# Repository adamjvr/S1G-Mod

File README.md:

# S1G-Mod
A Sub 1GHZ Wireless Module for various Sub 1GHZ projects and applications
Hardware Specs
- ADF7023 RF Transceiver
- 28 Mile line of site range
- Dedicated Antennas for RX and TX
- Open Source under CERN Open Hardware License v1.2 (Included)
- Circuitry shielded with outer shield.
- UM Coaxial Antenna connectors
- STM32L052C8T6 ARM Cortex M0+
- USB 2.0 connectivity
- USART connectivity
- SPI connectivity
- USB bus or battery powered
- Combined and Separate PA/LNA Match versions of 915MHZ and 433MHZ modules

Firmware and development at:
https://github.com/adamjvr/S1G-RF-firmwware

Combined RX/TX S1G-RF Module:

KiCAD 3D OpenGL

Separate RX/TX S1G-RF Module:

KiCAD 3D OpenGL

Adapters:

USART JST Adapter

SPI JST Adapter

Adapter Test Fit:

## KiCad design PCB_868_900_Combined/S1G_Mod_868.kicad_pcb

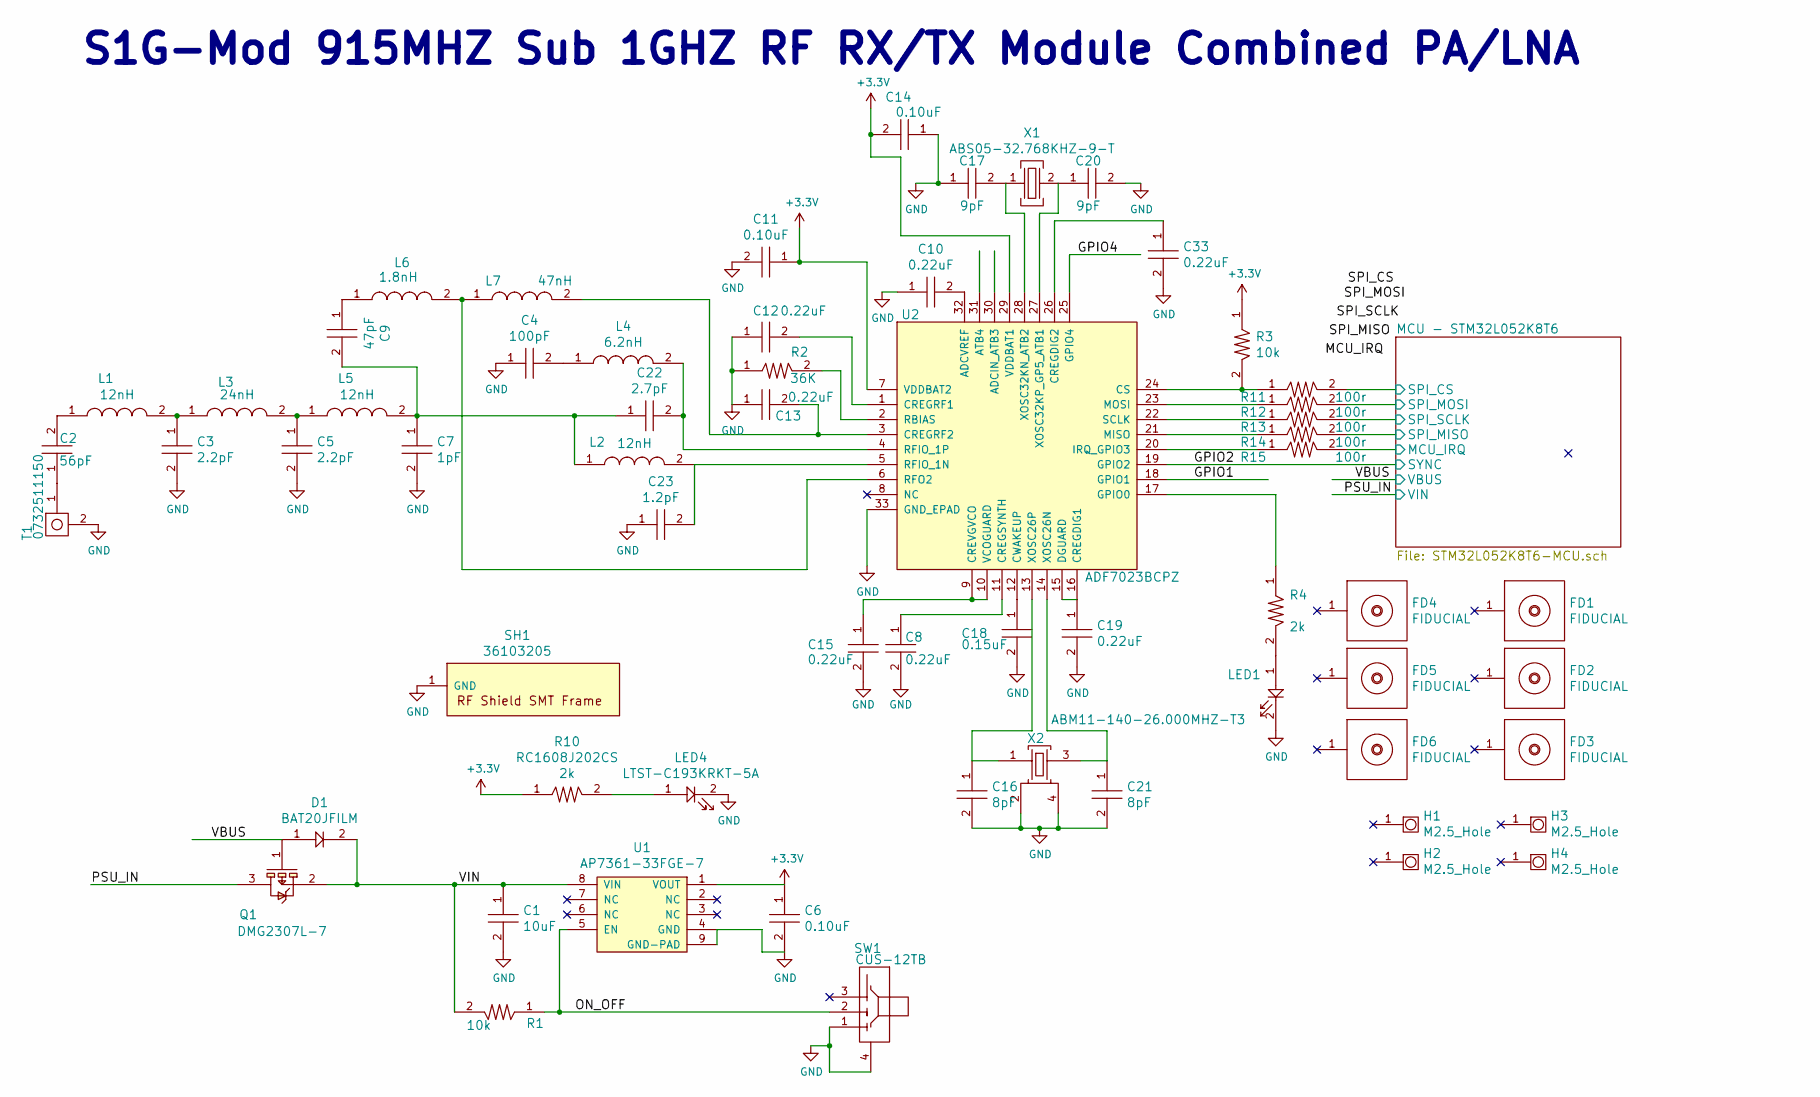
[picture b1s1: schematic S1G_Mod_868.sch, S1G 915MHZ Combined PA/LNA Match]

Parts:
C1: CL10A106KQ8NNNC; C0603; Tolerance 10%; Voltage 6.3V; MFR# CL10A106KQ8NNNC
C2: CBR04C560F1GAC; C0402; Tolerance 1%; Voltage 100V; MFR# CBR04C560F1GAC
C3, C5: GJM1555C1H2R2WB01D; C0402; Tolerance 0.05pF; Voltage 50V; MFR# GJM1555C1H2R2WB01D
C4: GRM1555C1H101GA01D; C0402; Tolerance 2%; Voltage 50V; MFR# GRM1555C1H101GA01D
C6, C11, C14: CL05B104JP5NNNC; C0402; Tolerance 5%; Voltage 10V; MFR# CL05B104JP5NNNC
C7: GJM1555C1H1R0BB01D; C0402; Tolerance 0.1pF; Voltage 50V; MFR# GJM1555C1H1R0BB01D
C8, C10, C12, C13, C15, C19, C33: CL05A224KP5NNNC; C0402; Tolerance 0.22uF; Voltage 16V; MFR# CL05A224KP5NNNC
C9: CBR04C470F3GAC; C0402; Tolerance 1%; Voltage 25V; MFR# CBR04C470F3GAC
C16, C21: GRM0225C1E8R0WA03L; C0402; Tolerance 0.05pF; Voltage 50V; MFR# GRM0225C1E8R0WA03L
C17, C20: CL05C090CB5NNNC; C0402; Tolerance 0.25pF; Voltage 50V; MFR# CL05C090CB5NNNC
C18: GRM155R71H152KA01D; C0402; Tolerance 10%; Voltage 50V; MFR# GRM155R71H152KA01D
C22: GRM1555C2A2R7CA01D; C0402; Tolerance 0.25pF; Voltage 50V; MFR# GRM1555C2A2R7CA01D
C23: GRM1555C1E1R2BA01D; C0402; Tolerance 0.1pF; Voltage 25V; MFR# GRM1555C1E1R2BA01D
D1: BAT20JFILM; Tolerance N/A; Voltage N/A; MFR# BAT20JFILM
FD1, FD2, FD3, FD4, FD5, FD6: FIDUCIAL
H1, H2, H3, H4: M2.5_Hole; M2.5_HOLE
L1, L2, L5: 0402CS-12NXJL; L0402; Tolerance 5%; Voltage N/A; MFR# 0402CS-12NXJL
L3: 0402CS-24NXJL; L0402; Tolerance 5%; Voltage N/A; MFR# 0402CS-24NXJL
L4: 0402CS-6N2XJL; L0402; Tolerance 5%; Voltage N/A; MFR# 0402CS-6N2XJL
L6: 0402CS-1N8XJL; L0402; Tolerance 5%; Voltage N/A; MFR# 0402CS-1N8XJL
L7: 0402CS-47NXJL; L0402; Tolerance 5%; Voltage N/A; MFR# 0402CS-47NXJL
LED1: LTST-C193TBKT-5A; LED0603; Tolerance N/A; Voltage 2.8V Forward Voltage; MFR# LTST-C193TBKT-5A
LED4: LTST-C193KRKT-5A; LED0603; Tolerance N/A; Voltage 2.8V Forward Voltage; MFR# LTST-C193KRKT-5A
Q1: DMG2307L-7; Tolerance N/A; Voltage 30V; MFR# DMG2307L-7
R1, R3: RC1005F103CS; R0402; Tolerance 1%; Voltage N/A; MFR# RC1005F103CS
R2: ERA-2AEB363X; R0402; Tolerance 0.1%; Voltage N/A; MFR# ERA-2AEB363X
R4, R10: RC1608J202CS; R0603; Tolerance 1%; Voltage N/A; MFR# RC1608F202CS
R11, R12, R13, R14, R15: TNPW0402100RBEED; R0402; Tolerance 0.1%; Voltage N/A; MFR# TNPW0402100RBEED
SH1: 36103205; Tolerance N/A; Voltage N/A; MFR# 36103205
SW1: CUS-12TB; Tolerance N/A; Voltage 50V 100mA; MFR# CUS-12TB
T1: 0732511150; Tolerance N/A; Voltage N/A; MFR# 0732511150
U1: AP7361-33FGE-7; Tolerance N/A; Voltage 3.3V; MFR# AP7361-33FGE-7
U2: ADF7023BCPZ; Tolerance N/A; Voltage 3.3V; MFR# ADF7023BCPZ
X1: ABS05-32.768KHZ-9-T; Tolerance ±20ppm; Voltage N/A; MFR# ABS05-32.768KHZ-9-T
X2: ABM11-140-26.000MHZ-T3; Tolerance N/A; Voltage N/A; MFR# ABM11-140-26.000MHZ-T3

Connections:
+3V3: C6.1, C11.1, C14.2, R3.1, R10.1, U1.1 (VOUT), U2.7 (VDDBAT2), U2.29 (VDDBAT1); also elsewhere on the board
/GPIO1: U2.18 (GPIO1)
/GPIO2: U2.19 (GPIO2); also elsewhere on the board
/GPIO4: U2.25 (GPIO4)
/MCU - STM32L052K8T6/MCU_IRQ: R15.2; also elsewhere on the board
/MCU - STM32L052K8T6/SPI_CS: R11.2; also elsewhere on the board
/MCU - STM32L052K8T6/SPI_MISO: R14.2; also elsewhere on the board
/MCU - STM32L052K8T6/SPI_MOSI: R12.2; also elsewhere on the board
/MCU - STM32L052K8T6/SPI_SCLK: R13.2; also elsewhere on the board
/ON_OFF: R1.1, SW1.2, U1.5 (EN)
/PSU_IN: Q1.3; also elsewhere on the board
/VBUS: D1.1, Q1.1; also elsewhere on the board
/VIN: C1.1, D1.2, Q1.2, R1.2, U1.8 (VIN)
GND: C1.2, C3.2, C4.1, C5.2, C6.2, C7.2, C8.2, C10.1, C11.2, C12.1, C13.1, C14.1, C15.2, C16.2, C17.1, C18.2, C19.2, C20.2, C21.2, C23.1, C33.2, LED1.2, LED4.2, R2.1, SH1.1, SW1.1, SW1.4, T1.2, U1.4 (GND), U1.9 (GND-PAD), U2.33 (GND_EPAD), X2.2, X2.4; also elsewhere on the board
unnamed: C2.1, T1.1
unnamed: C2.2, L1.1
unnamed: C3.1, L1.2, L3.1
unnamed: C4.2, L4.1
unnamed: C5.1, L3.2, L5.1
unnamed: C8.1, U2.11 (CREGSYNTH)
unnamed: C9.1, L6.1
unnamed: C10.2, U2.32 (ADCVREF)
unnamed: C12.2, U2.1 (CREGRF1)
unnamed: C13.2, L7.2, U2.3 (CREGRF2)
unnamed: C15.1, U2.9 (CREVGVCO), U2.10 (VCOGUARD)
unnamed: C16.1, U2.13 (XOSC26P), X2.1
unnamed: C17.2, U2.28 (XOSC32KN_ATB2), X1.1
unnamed: C18.1, U2.12 (CWAKEUP)
unnamed: C19.1, U2.15 (DGUARD), U2.16 (CREGDIG1)
unnamed: C20.1, U2.27 (XOSC32KP_GP5_ATB1), X1.2
unnamed: C21.1, U2.14 (XOSC26N), X2.3
unnamed: C7.1, C9.2, C22.1, L2.1, L5.2
unnamed: C22.2, L4.2, U2.4 (RFIO_1P)
unnamed: C23.2, L2.2, U2.5 (RFIO_1N)
unnamed: C33.1, U2.26 (CREGDIG2)
unnamed: L6.2, L7.1, U2.6 (RFO2)
unnamed: LED1.1, R4.2
unnamed: LED4.1, R10.2
unnamed: R2.2, U2.2 (RBIAS)
unnamed: R4.1, U2.17 (GPIO0)
unnamed: R3.2, R11.1, U2.24 (CS)
unnamed: R12.1, U2.23 (MOSI)
unnamed: R13.1, U2.22 (SCLK)
unnamed: R14.1, U2.21 (MISO)
unnamed: R15.1, U2.20 (IRQ_GPIO3)

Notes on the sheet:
S1G-Mod 915MHZ Sub 1GHZ RF RX/TX Module Combined PA/LNA

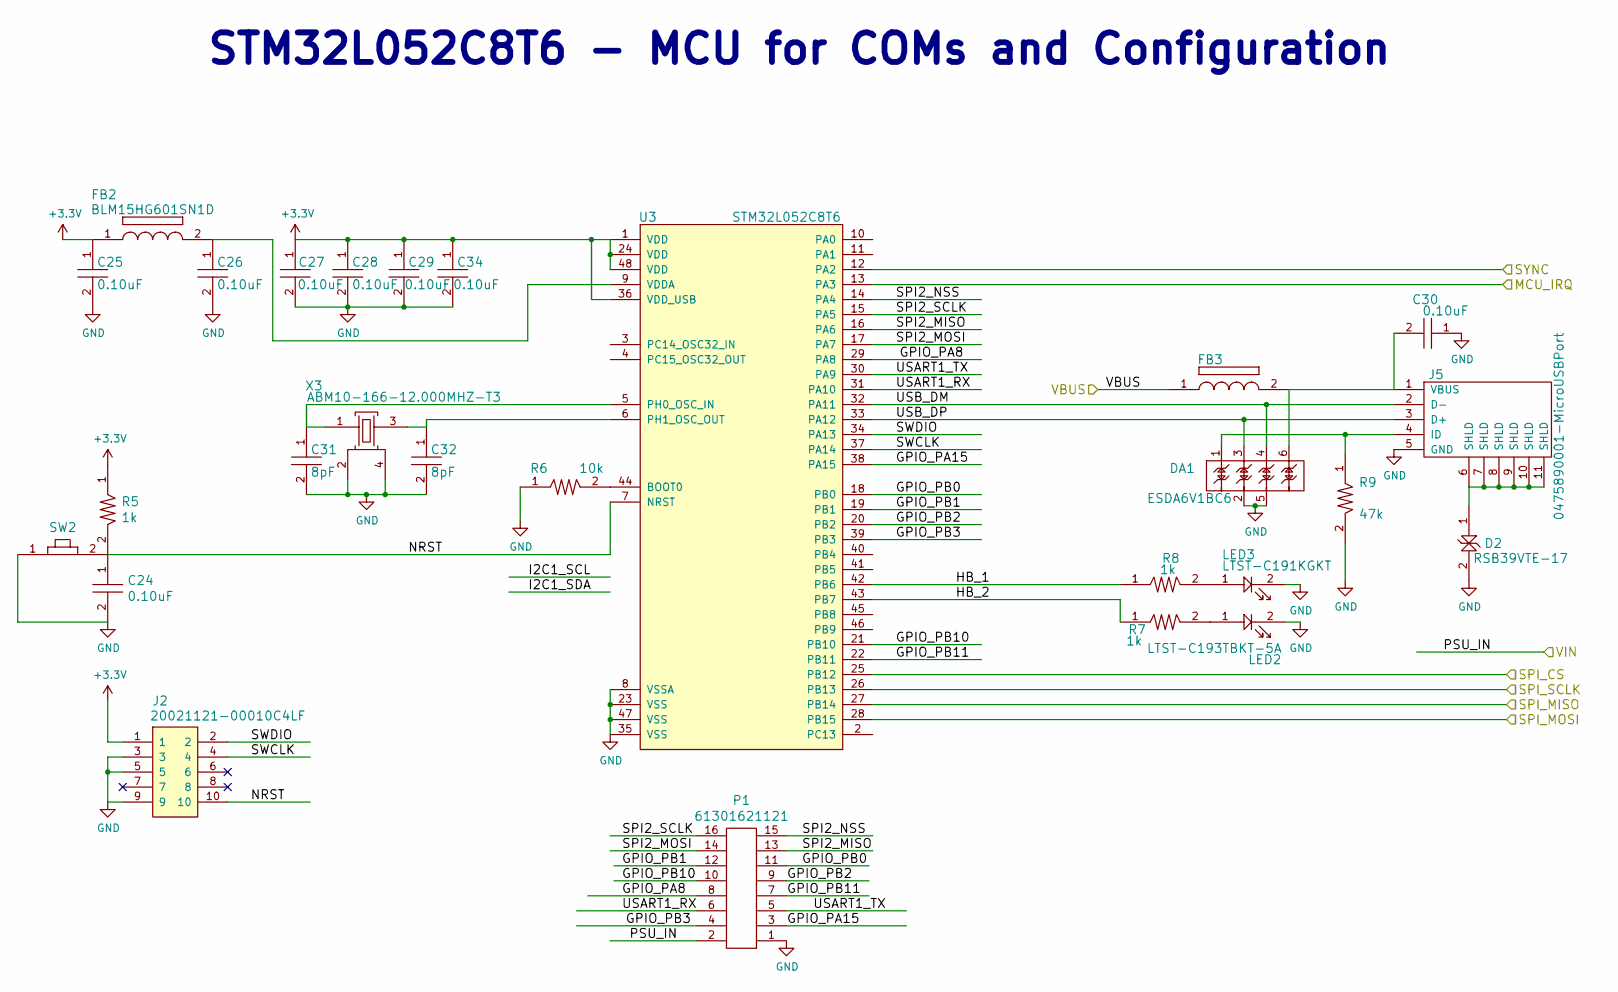
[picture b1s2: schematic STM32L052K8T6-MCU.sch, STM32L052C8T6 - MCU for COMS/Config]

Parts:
C24, C25, C26, C27, C28, C29, C30, C34: CL05B104JP5NNNC; C0402; Tolerance 5%; Voltage 10V; MFR# CL05B104JP5NNNC
C31, C32: GRM0225C1E8R0WA03L; C0402; Tolerance 0.05pF; Voltage 50V; MFR# GRM0225C1E8R0WA03L
D2: RSB39VTE-17; Tolerance N/A; Voltage 30V; MFR# RSB39VTE-17
DA1: ESDA6V1BC6; Tolerance N/A; Voltage 4V; MFR# ESDA6V1BC6
FB2: BLM15HG601SN1D; Tolerance N/A; Voltage N/A; MFR# BLM15HG601SN1D
FB3: MI0603K300R-10; Tolerance N/A; Voltage N/A; MFR# MI0603K300R-10
J2: 20021121-00010C4LF; Tolerance N/A; Voltage 200V MAX; MFR# 20021121-00010C4LF
J5: 0475890001-MicroUSBPort; 0475890001; Tolerance N/A; Voltage 5V; MFR# 0475890001
LED2: LTST-C193TBKT-5A; LED0603; Tolerance N/A; Voltage 2.8V Forward Voltage; MFR# LTST-C193TBKT-5A
LED3: LTST-C191KGKT; LED0603; Tolerance N/A; Voltage N/A; MFR# LTST-C191KGKT
P1: 61301621121; Tolerance N/A; Voltage N/A; MFR# B3B-PH-SM4-TB(LF)(SN)
R5, R7, R8: RC1005F102CS; R0402; Tolerance %; Voltage N/A; MFR# RC1005F102CS
R6: RC1005F103CS; R0402; Tolerance 1%; Voltage N/A; MFR# RC1005F103CS
R9: RC1005J473CS; R0402; Tolerance 5%; Voltage N/A; MFR# RC1005J473CS
SW2: B3U-1000P; Tolerance %; Voltage 50V; MFR# B3U-1000P
U3: STM32L052C8T6; Tolerance N/A; Voltage 1.8-3.3V; MFR# STM32L052C8T6
X3: ABM10-166-12.000MHZ-T3; Tolerance N/A; Voltage N/A; MFR# ABM10-166-12.000MHZ-T3

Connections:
+3V3: C25.1, C27.1, C28.1, C29.1, C34.1, FB2.1, J2.1, R5.1, U3.1 (VDD), U3.24 (VDD), U3.36 (VDD_USB), U3.48 (VDD); also elsewhere on the board
/GPIO2: U3.12 (PA2); also elsewhere on the board
/MCU - STM32L052K8T6/GPIO_PA8: P1.8, U3.29 (PA8)
/MCU - STM32L052K8T6/GPIO_PA15: P1.3, U3.38 (PA15)
/MCU - STM32L052K8T6/GPIO_PB0: P1.11, U3.18 (PB0)
/MCU - STM32L052K8T6/GPIO_PB1: P1.12, U3.19 (PB1)
/MCU - STM32L052K8T6/GPIO_PB2: P1.9, U3.20 (PB2)
/MCU - STM32L052K8T6/GPIO_PB3: P1.4, U3.39 (PB3)
/MCU - STM32L052K8T6/GPIO_PB10: P1.10, U3.21 (PB10)
/MCU - STM32L052K8T6/GPIO_PB11: P1.7, U3.22 (PB11)
/MCU - STM32L052K8T6/HB_1: R8.1, U3.42 (PB6)
/MCU - STM32L052K8T6/HB_2: R7.1, U3.43 (PB7)
/MCU - STM32L052K8T6/MCU_IRQ: U3.13 (PA3); also elsewhere on the board
/MCU - STM32L052K8T6/NRST: C24.1, J2.10, R5.2, SW2.2, U3.7 (NRST)
/MCU - STM32L052K8T6/SPI2_MISO: P1.13, U3.16 (PA6)
/MCU - STM32L052K8T6/SPI2_MOSI: P1.14, U3.17 (PA7)
/MCU - STM32L052K8T6/SPI2_NSS: P1.15, U3.14 (PA4)
/MCU - STM32L052K8T6/SPI2_SCLK: P1.16, U3.15 (PA5)
/MCU - STM32L052K8T6/SPI_CS: U3.25 (PB12); also elsewhere on the board
/MCU - STM32L052K8T6/SPI_MISO: U3.27 (PB14); also elsewhere on the board
/MCU - STM32L052K8T6/SPI_MOSI: U3.28 (PB15); also elsewhere on the board
/MCU - STM32L052K8T6/SPI_SCLK: U3.26 (PB13); also elsewhere on the board
/MCU - STM32L052K8T6/SWCLK: J2.4, U3.37 (PA14)
/MCU - STM32L052K8T6/SWDIO: J2.2, U3.34 (PA13)
/MCU - STM32L052K8T6/USART1_RX: P1.6, U3.31 (PA10)
/MCU - STM32L052K8T6/USART1_TX: P1.5, U3.30 (PA9)
/MCU - STM32L052K8T6/USB_DM: DA1.4, J5.2 (D-), U3.32 (PA11)
/MCU - STM32L052K8T6/USB_DP: DA1.3, J5.3 (D+), U3.33 (PA12)
/PSU_IN: P1.2; also elsewhere on the board
/VBUS: FB3.1; also elsewhere on the board
GND: C24.2, C25.2, C26.2, C27.2, C28.2, C29.2, C30.1, C31.2, C32.2, C34.2, D2.2, DA1.2, DA1.5, J2.3, J2.5, J2.9, J5.5 (GND), LED2.2, LED3.2, P1.1, R6.1, R9.2, SW2.1, U3.8 (VSSA), U3.23 (VSS), U3.35 (VSS), U3.47 (VSS), X3.2, X3.4; also elsewhere on the board
unnamed: C26.1, FB2.2, U3.9 (VDDA)
unnamed: C30.2, DA1.6, FB3.2, J5.1 (VBUS)
unnamed: C31.1, U3.5 (PH0_OSC_IN), X3.1
unnamed: C32.1, U3.6 (PH1_OSC_OUT), X3.3
unnamed: D2.1, J5.6 (SHLD), J5.7 (SHLD), J5.8 (SHLD), J5.9 (SHLD), J5.10 (SHLD), J5.11 (SHLD)
unnamed: DA1.1, J5.4 (ID), R9.1
unnamed: LED2.1, R7.2
unnamed: LED3.1, R8.2
unnamed: R6.2, U3.44 (BOOT0)

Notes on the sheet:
STM32L052C8T6 - MCU for COMs and Configuration

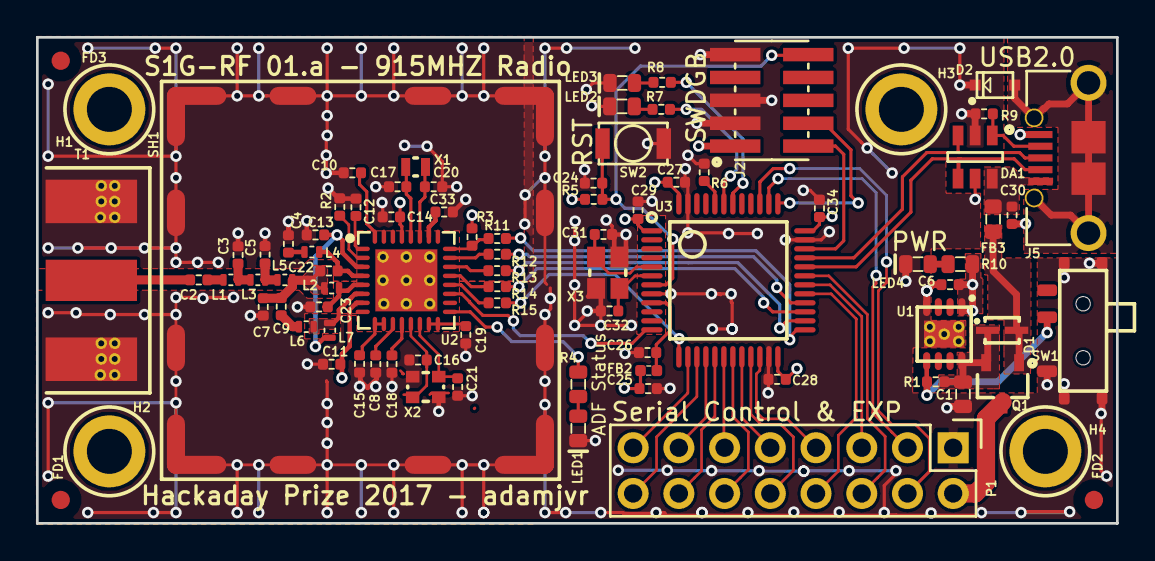
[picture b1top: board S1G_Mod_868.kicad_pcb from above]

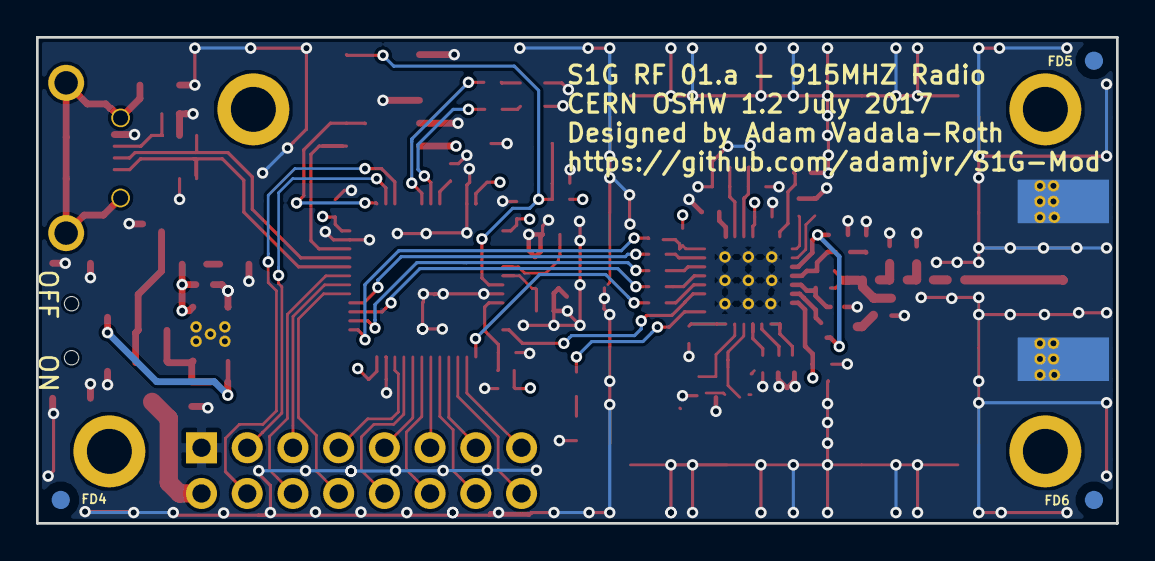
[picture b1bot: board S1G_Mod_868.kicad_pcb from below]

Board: 4 copper layers, 60.0 x 27.0 mm, 89 parts (3 on the bottom side), 73 nets.

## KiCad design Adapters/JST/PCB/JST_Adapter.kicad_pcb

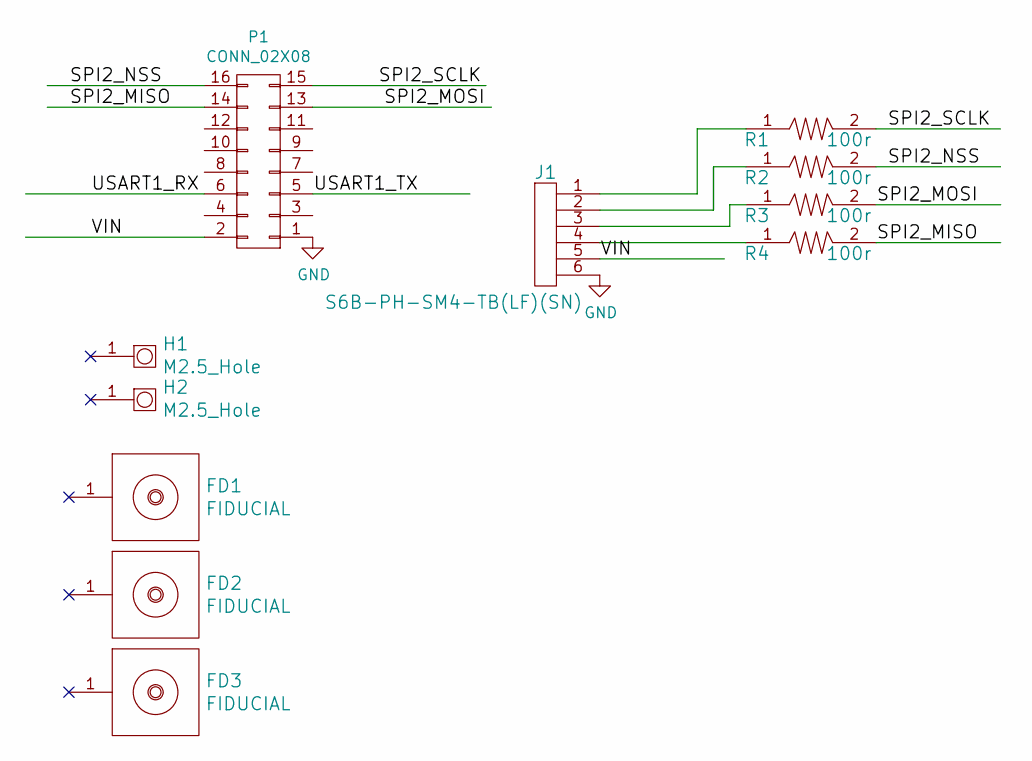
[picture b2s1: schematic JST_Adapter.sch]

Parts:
FD1, FD2, FD3: FIDUCIAL
H1, H2: M2.5_Hole; M2.5_HOLE
J1: S6B-PH-SM4-TB(LF)(SN); Tolerance N/A; Voltage N/A; MFR# S6B-PH-SM4-TB(LF)(SN)
P1: CONN_02X08; Socket_Strip_Straight_2x08
R1, R2, R3, R4: TNPW0402100RBEED; R0402; Tolerance 0.1%; Voltage N/A; MFR# TNPW0402100RBEED

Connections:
/SPI2_MISO: P1.14, R4.2
/SPI2_MOSI: P1.13, R3.2
/SPI2_NSS: P1.16, R2.2
/SPI2_SCLK: P1.15, R1.2
/USART1_RX: P1.6
/USART1_TX: P1.5
/VIN: J1.5, P1.2
GND: J1.6, P1.1
unnamed: J1.1, R1.1
unnamed: J1.2, R2.1
unnamed: J1.3, R3.1
unnamed: J1.4, R4.1

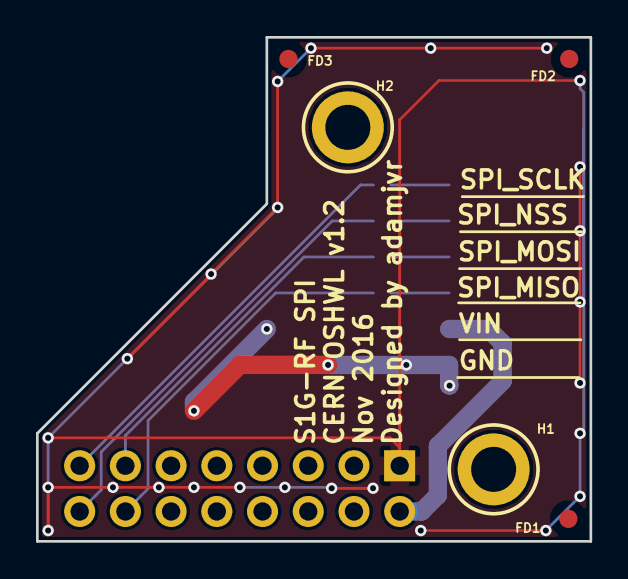
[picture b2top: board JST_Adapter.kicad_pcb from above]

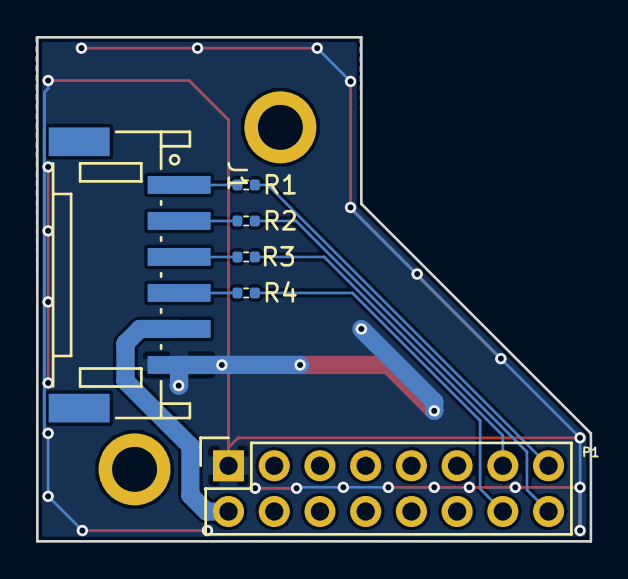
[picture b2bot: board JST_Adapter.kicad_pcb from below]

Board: 2 copper layers, 30.8 x 28.0 mm, 11 parts (6 on the bottom side), 10 nets.

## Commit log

2016-10-30 Initial Commit
    Schematic and Kicad project created for the three different versions of
    the module.
2016-10-31 868MHZ
    Significant progress made with 868MHZ schematic, near complete just
    researching the output section more before commiting to component and
    circuit choices.
2016-10-31 PCB Created
    PCB created and placemetn started. Going to be a more robust
    implementatinn of XBee pro but bigger formfactor. going to require dual
    antennas or external mixrer (perhaps another PCB "? )
2016-11-07 Progress and reorganized
    project reorganized separate PA/LNA version near done, added an M0+ MCU.
2016-11-08 Change and Progress
    connecotrs change to SMA, implemented combined PA/LNA match, currently
    working on that version as primary. PCB components are placed and board
    size is almost set.
2016-11-10 RF Shield and more progress
    Adding an RF shield to the combined implementation of the 915MHZ version
    of S1G. Also experimenting with differnt connectors and what not.
2016-11-10 First pass on PCB
    First pass on PCB completed. PCB_868_900_Combined is the folder for the
    finished rev.
2016-11-10 Cleaner routing
    Cleaned up routing and improved copper pours in the RF section. Need to
    do a bit more research on how much fill is necessary with a 4 layer
    board.
2016-11-11 License added and dedicated PA/LNA Match
    Working on the separate PA/LNA match version. also added cern license
2016-11-11 Progress
    Significant progress on the separate PA/LNA matchj implementation.
    Formfactor has been devised and is similar to the combined version , so
    they go together well. Component placement is mostly complete and board
    outline solidified.
2016-11-11 Separate PA/LNA first pass
    first pass on PCB complete !
2016-11-12 PCBs Tweaked A lot
    PCBs have been tweaked. The separate implementation has been finished
    but also has GPIOs from the MCU broken out to the connector, same for
    the combined implementation. Both boards now have power indication LEDs
    (red).
2016-11-14 Grounding and Adapter
    Grounding changed on both versions of the 915MHZ/868MHZ versions of the
    radio both the combined and separate antenna versions. Also an adapter
    is being developed for alternative connection options.
2016-11-14 adapter finished
    finished adapter
2016-11-14 Via Stitching
    Ground pour stiching applied to the combined PA/LNA match version of the
    915MHZ radio. All ground pours and layers are now stiched together
    effectively.
2016-11-14 Separate Antenna Via Stiching
    The S1G implementation with separate antennas and matching circuitry has
    been thoroughly stiched with vias linking all ground pours to the
    internal plane with a significant amunt of connection points.
2016-11-14 Additional GPIO
    Two additional GPIO pins from the STM32L0 have been added to the
    connector, now there is a signal on every pin. The connector component
    has been replaced with one that has a STEP 3D model for proper 3D model
    exporting from KiCAD for enclosure design. This has been done to both
    versions of the radio.
2016-11-15 Adapters
    Adapter ended up being too large. So I split it into two separate
    adapters one for SPI and one for USART over JST connectors. SPI board
    has 100 ohm inline resistors for EMI and impedance matching in case the
    driving device lacks these internally or on its board. Additional
    Fudicials added to the combined implementation.
2016-11-15 LDO and Pwr LEd
    Power LED added to combined radio and LDO section revamped.
2016-11-15 More LDO
    LDO section on separate antenna version retooled to be more like the
    combined antenna version. Added additional fudicials on the bottom.
2016-11-15 SPI Resistors
    Added 100 ohm inline resistors with SPI line and IRQ signal between
    ADF7023 and STM32L0 on the separate antenna implementation.
2016-11-15 SPI Resistors
    SPI resistors added to combined antenna implementation.
2016-11-15 DRC Check
    DRC check run and all errors cleared on separate anatenna implmentation.
    Nearing time to fabricate.
2016-11-15 DRC Check Combined
    DRC Check run on combined implementation. All errors cleared,
    fabrication soon.
2016-11-16 Readme
    Readme updated and boms exported.
2016-11-16 Readme
    Readme updated with images.
2016-11-17 USB VDD
    Found schematic bug, USB VDD was not tied to 3V3 supply or applied a
    bypass cap, this has been resolved in both implementations of the S1G.
    STM32L0 program manual added to the datasheets collection for the
    project. Schematic PDFs updated.
2016-11-20 More Stitching and readme
    Added more via stitching to separate RX/TX implementation. More vias
    near the pin connector like the combined version. Also added a link to
    the firmware repo on the readme.
2016-12-06 0.22uF cap
    0.22uF cap replaced with 0402 part instead of the massive 0603 part.
2017-07-16 Radio Reference Schematic Errors
    Some errors transcribing ADI's reference shcematic. 0.22uF caps added to
    pins that needed it etc.
2017-07-27 PDF
    schematic exported as color PDF for review
